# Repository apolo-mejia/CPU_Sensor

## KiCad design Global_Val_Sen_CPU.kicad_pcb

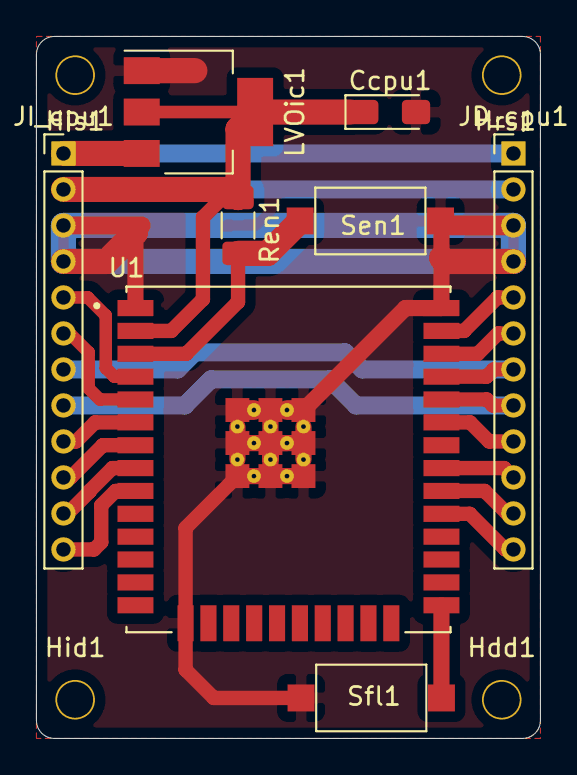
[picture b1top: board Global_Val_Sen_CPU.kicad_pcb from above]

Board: 2 copper layers, 28.0 x 39.0 mm, 12 parts (0 on the bottom side), 19 nets.

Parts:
Ccpu1: C; CP_EIA-3216-10_Kemet-I_Pad1.58x1.35mm_HandSolder
Hdd1: MH; MountingHole_2.2mm_M2_DIN965
Hid1: MH; MountingHole_2.2mm_M2_DIN965
His1: MH; MountingHole_2.2mm_M2_DIN965
Hrs1: MH; MountingHole_2.2mm_M2_DIN965
JD_cpu1: Conn_01x12; PinHeader_1x12_P2.00mm_Vertical
JI_cpu1: Conn_01x12; PinHeader_1x12_P2.00mm_Vertical
LVOic1: LD1117S33TR_SOT223; SOT-223-3_TabPin2
Ren1: 9.1k; R_1206_3216Metric_Pad1.30x1.75mm_HandSolder
Sen1: SW_DIP_x01; SW_SPST_CK_RS282G05A3
Sfl1: SW_DIP_x01; SW_SPST_CK_RS282G05A3
U1: CPU1; ESP32-WROOM-32U

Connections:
+3V3: Ccpu1.1, JD_cpu1.2, JI_cpu1.2, LVOic1.2, Ren1.1, U1.2
+5V: JD_cpu1.1, JI_cpu1.1, LVOic1.3
CLK: JD_cpu1.11, U1.30
CS: JD_cpu1.12, U1.29
GND: Ccpu1.2, JD_cpu1.3, JD_cpu1.4, JI_cpu1.3, JI_cpu1.4, LVOic1.1, Sen1.1, Sfl1.1, U1.1, U1.15, U1.38, U1.G.1, U1.G.2, U1.G.4, U1.G.5, U1.G.6, U1.G.7, U1.G.8, U1.G.9, U1.G.10, U1.G.11, U1.G.12, U1.G.13, U1.G.14, U1.G.15, U1.G.16, U1.G.17, U1.G.18, U1.G.19, U1.G.20, U1.G.21, U1.G.22
I34: JI_cpu1.9, U1.6
I35: JI_cpu1.10, U1.7
IO32: JI_cpu1.11, U1.8
IO33: JI_cpu1.12, U1.9
MISO: JD_cpu1.10, U1.31
MOSI: JD_cpu1.5, U1.37
unnamed: Ren1.2, Sen1.2, U1.3
unnamed: Sfl1.2, U1.25
RX: JD_cpu1.8, JI_cpu1.8, U1.34
SCL0: JD_cpu1.6, U1.36
SDA0: JD_cpu1.9, U1.33
S_VN: JI_cpu1.6, U1.5
S_VP: JI_cpu1.5, U1.4
TX: JD_cpu1.7, JI_cpu1.7, U1.35

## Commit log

2022-11-27 Cargardo Version Inicial
